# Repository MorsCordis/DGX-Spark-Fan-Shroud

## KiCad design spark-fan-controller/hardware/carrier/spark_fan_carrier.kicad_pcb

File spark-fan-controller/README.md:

# Spark fan controller

External 120 mm fan control for NVIDIA DGX Spark boxes in the
[DGX-Spark-Fan-Shroud](https://github.com/hyudryu/DGX-Spark-Fan-Shroud) (fork: MorsCordis).
The host service feeds the fan forward from GPU/CPU load with a temperature fallback.

## Layout

| Path | What |
|---|---|
| `host/spark_fan.py`, `host/spark-fan.service` | Host controller (runs on each Spark). Load-anticipating curve + thermal fallback, serial `DUTY 0..255` |
| `firmware/main_pwm_carrier.py` | MicroPython for the **Spark Fan Carrier** (GP28 PWM via open-drain FET, GP29 tach) |
| `firmware/main_x9c103.py` | Original repo firmware for the X9C103 + Owltree build (box #1) |
| `hardware/carrier/` | Spark Fan Carrier rev A: KiCad 10 schematic + PCB, generated from `design.py` |
| `hardware/carrier/fab/` | JLCPCB upload: `spark_fan_carrier_gerbers.zip`, `bom_jlc.csv`, `cpl_jlc.csv`, `bom_hand_solder.csv` |
| `hardware/enclosure/carrier_case.scad` | Parametric 3D-printed case for the carrier (+ `stl/`) |
| `hardware/enclosure/fan_guard.scad` | Bolt-on 120 mm intake guard + filter pocket + retainer (+ `stl/`, `stl/filter_template.svg`) |
| `hardware/enclosure/x9c103_box.scad` | Case for the original three-board build |
| `tests/` | `prefill_stress.py` (long-context prefill ramp via vLLM), `llm_stress.py`, `cooling_test.py` |
| `docs/` | Forum write-ups, stress logs, build guide for the X9C103 build |

## Spark Fan Carrier (rev A)

RP2040-Zero plugs into two 1x9 sockets. Its USB 5 V feeds an MT3608 boost to 12.36 V
(100k/5.1k feedback) for a 4-pin PWM fan header. GP28 drives fan pin 4 through a 2N7002
(open drain, inverted, gate pulled down, so a dead or unflashed RP2040 means full speed).
GP29 reads the tach through 1k with a 10k pull-up and 1 nF filter. 1.5 A PTC on the 5 V input,
green LED on 12 V. 24 x 50 mm, two layers, GND pour both sides, two M2.5 holes.

Rebuild everything (KiCad's bundled python):

```
cd hardware/carrier
"%LOCALAPPDATA%\Programs\KiCad\10.0\bin\python.exe" gen_sch.py
"%LOCALAPPDATA%\Programs\KiCad\10.0\bin\python.exe" gen_pcb.py
"%LOCALAPPDATA%\Programs\KiCad\10.0\bin\python.exe" fab.py
```

`design.py` is the single source for parts and nets; `gen_pcb.py` holds placement and routing.
Last check: ERC 0 violations, DRC 0 errors / 0 unconnected, schematic parity clean (remaining
warnings are silkscreen overlaps from the stock socket footprints).

Ordering at JLC (the board has SMD parts that are NOT practical to hand-solder, including the
MT3608, which DigiKey doesn't carry):
1. Upload `fab/spark_fan_carrier_gerbers.zip` (2 layers, 1.6 mm).
2. **Turn on "PCB Assembly"** below the board options. Without it JLC ships bare boards.
   Economic PCBA, top side, PCBA qty can be lower than the board qty.
3. Upload `fab/bom_jlc.csv` (BOM) and `fab/cpl_jlc.csv` (placement).
4. Check every part is matched, then check rotations in the placement preview (D1, D2, U1, Q1).

Before ordering:
- All 16 LCSC numbers in `fab/bom_jlc.csv` checked against JLC part pages on 2026-10-24
  (values, packages and ratings match). MT3608 and the LED are Extended parts.
- Check part rotations in JLC's placement preview (KiCad and JLC disagree on some footprints).
- J1/J2 (1x9 female, ~8.5 mm) and J3 (4-pin fan header) are hand-soldered.

Firmware: flash MicroPython, copy `firmware/main_pwm_carrier.py` to the board as `main.py`.
`host/spark_fan.py` works unchanged and now gets real `RPM` readings.

## Enclosure

`carrier_case.scad`: base + friction-fit lid, prints without supports (lid prints upside down).
USB-C opening, fan-cable slot, mounting ears, pinholes over BOOT/RESET. No screws: pegs on the
standoffs pass through H1/H2 and posts on the lid clamp the board (`fix = "screw"` restores
M2.5 self-tap pilots). Light pipes: Bivar PLPC2 press-fit from the top of the lid
(PLPC2-3MM over the Zero's RGB LED, PLPC2-500 over the 12 V LED, 2.0 mm hole with Bivar's
countersink); `pipes = "filament"` switches to clear 1.75 mm filament. Values marked `MEASURE`
(socket height, Zero LED/button positions) should be checked against real parts.
Outer size ~28.8 x 54.8 x 24.3 mm.

## Purchased parts

`hardware/bom_digikey_per_build.csv` is the DigiKey order for one build (carrier through-hole
parts, light pipes, fan guard magnets + filter, cable). Upload it in DigiKey's BOM Manager and
set the number of assemblies. The JLC-assembled SMD parts are in
`hardware/carrier/fab/bom_jlc.csv`; `hardware/carrier/fab/bom_digikey_smd.csv` is a DigiKey
fallback for hand assembly (no MT3608: DigiKey doesn't carry it; get it from LCSC C84817). RP2040-Zero boards come from Waveshare (not on DigiKey).

## Fan guard + filter

`fan_guard.scad`: hex grille plate that snaps onto the fan's intake side magnetically.
Default (`mount = "screw_head"`): drive the fan's bundled steel screws into the intake end of
the four holes; their heads sit in recesses on the guard's fan face (which also locate it) and
a 1/4" x 1/8" disc magnet (Radial Magnets 8193) sealed above each recess grabs them. Print fan-face down, pause at
z = 6.8 mm, drop the magnets in, resume. Measure the screw head (`head`, marked MEASURE) first.
`mount = "magnet"` glues 4 mm magnets into the holes instead (`stl/fan_guard_magnet.stl`, pause
at 4.0 mm; set polarity by sticking pairs together and marking the exposed face).
`mount = "screw"` is the bolt-on version (`stl/fan_guard_screw.stl`). An octagonal rim forms a pocket for a filter
up to `filter_max` (6.5 mm) thick; the retainer grid's skirt slides over the rim and stops on
the filter, so thin mesh and 1/4" foam both work. Adds 11.1 mm below the fan. Cut the
filter from `stl/filter_template.svg` (print at 100 %). Both parts print flat, no supports.

## To do

- [ ] Order carrier rev A, build, flash, bench test (12 V rail, PWM sweep, tach)
- [ ] Print + fit-check fan guard (fan hole diameter vs magnet, retainer `fit`)
- [ ] Multi-box dashboard (status endpoint in `spark_fan.py`)
- [ ] Filter-on vs filter-off prefill run at 2400 MHz
- [ ] Carrier, case, fan guard and carrier firmware stay private (possible product). Only the load-boost software is public (fork branch `feature/load-boost-controller`)

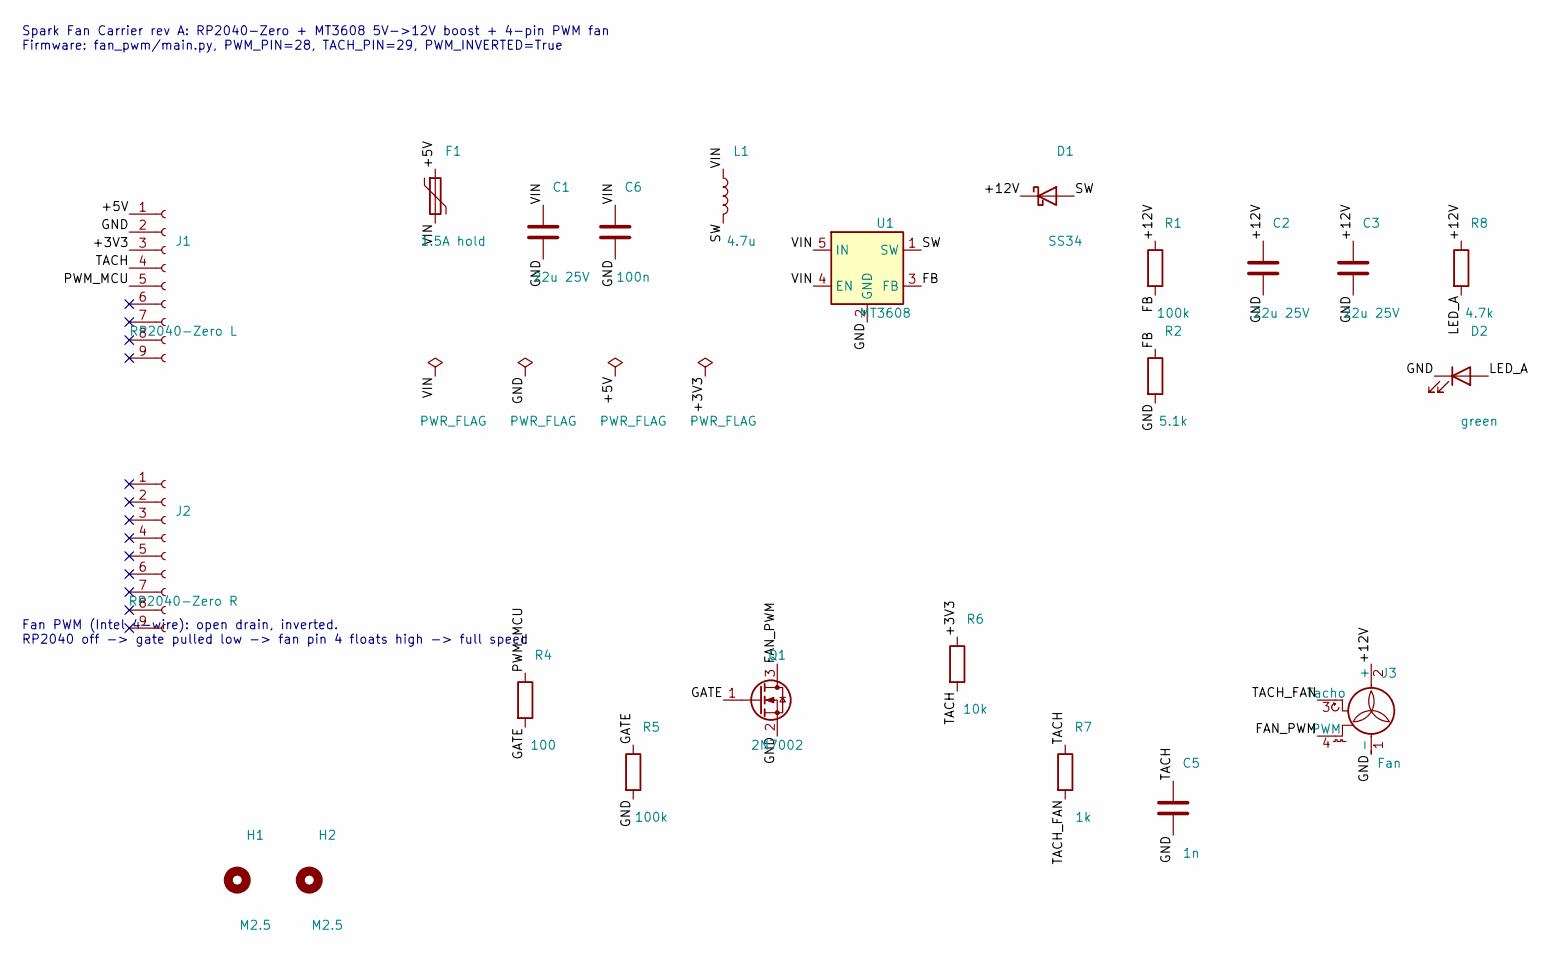
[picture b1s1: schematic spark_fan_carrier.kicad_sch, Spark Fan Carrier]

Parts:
C1: 22u 25V; C_0805_2012Metric; LCSC C45783
C2, C3: 22u 25V; C_1206_3216Metric; LCSC C12891
C5: 1n; C_0603_1608Metric; LCSC C1588
C6: 100n; C_0603_1608Metric; LCSC C14663
D1: SS34; D_SMA; LCSC C8678
D2: green; LED_0603_1608Metric; LCSC C72043
F1: 1.5A hold; Fuse_1206_3216Metric; MPN Eaton PTS12066V150; LCSC C2442501
H1, H2: M2.5; MountingHole_2.7mm_M2.5
J1: RP2040-Zero L; PinSocket_1x09_P2.54mm_Vertical
J2: RP2040-Zero R; PinSocket_1x09_P2.54mm_Vertical
J3: Fan; FanPinHeader_1x04_P2.54mm_Vertical
L1: 4.7u; L_Sunlord_SWPA5040S; MPN Sunlord SWPA5040S4R7MT; LCSC C48496
Q1: 2N7002; SOT-23; LCSC C8545
R1, R5: 100k; R_0603_1608Metric; LCSC C25803
R2: 5.1k; R_0603_1608Metric; LCSC C23186
R4: 100; R_0603_1608Metric; LCSC C22775
R6: 10k; R_0603_1608Metric; LCSC C25804
R7: 1k; R_0603_1608Metric; LCSC C21190
R8: 4.7k; R_0603_1608Metric; LCSC C23162
U1: MT3608; SOT-23-6; LCSC C84817

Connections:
/+3V3: J1.3, R6.1
/+5V: F1.1, J1.1
/+12V: C2.1, C3.1, D1.1 (K), J3.2 (+), R1.1, R8.1
/FAN_PWM: J3.4 (PWM), Q1.3 (D)
/FB: R1.2, R2.1, U1.3 (FB)
/GATE: Q1.1 (G), R4.2, R5.1
/GND: C1.2, C2.2, C3.2, C5.2, C6.2, D2.1 (K), J1.2, J3.1 (-), Q1.2 (S), R2.2, R5.2, U1.2 (GND)
/LED_A: D2.2 (A), R8.2
/PWM_MCU: J1.5, R4.1
/SW: D1.2 (A), L1.2, U1.1 (SW)
/TACH: C5.1, J1.4, R6.2, R7.1
/TACH_FAN: J3.3 (Tacho), R7.2
/VIN: C1.1, C6.1, F1.2, L1.1, U1.4 (EN), U1.5 (IN)

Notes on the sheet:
Spark Fan Carrier rev A: RP2040-Zero + MT3608 5V->12V boost + 4-pin PWM fan Firmware: fan_pwm/main.py, PWM_PIN=28, TACH_PIN=29, PWM_INVERTED=True
Fan PWM (Intel 4-wire): open drain, inverted. RP2040 off -> gate pulled low -> fan pin 4 floats high -> full speed

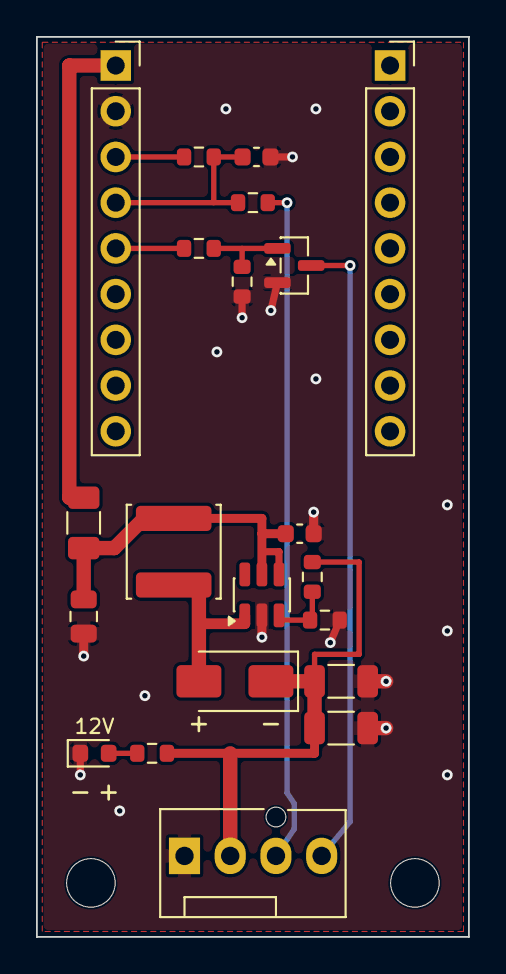
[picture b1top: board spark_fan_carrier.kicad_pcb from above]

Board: 2 copper layers, 24.0 x 50.0 mm, 23 parts (0 on the bottom side), 13 nets.

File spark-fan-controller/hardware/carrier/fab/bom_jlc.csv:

Comment,Designator,Footprint,LCSC Part #,MPN / note
22u 25V,C1,C_0805_2012Metric,C45783,
22u 25V,"C2,C3",C_1206_3216Metric,C12891,
1n,C5,C_0603_1608Metric,C1588,
100n,C6,C_0603_1608Metric,C14663,
SS34,D1,D_SMA,C8678,
red,D2,LED_0603_1608Metric,C2286,
1.5A hold,F1,Fuse_1206_3216Metric,C20802,Ruilon SMD1206P150TF
4.7u,L1,L_Sunlord_SWPA5040S,C48496,Sunlord SWPA5040S4R7MT
2N7002,Q1,SOT-23,C8545,
100k,"R1,R5",R_0603_1608Metric,C25803,
5.1k,R2,R_0603_1608Metric,C23186,
100,R4,R_0603_1608Metric,C22775,
10k,R6,R_0603_1608Metric,C25804,
1k,R7,R_0603_1608Metric,C21190,
4.7k,R8,R_0603_1608Metric,C23162,
MT3608,U1,SOT-23-6,C84817,

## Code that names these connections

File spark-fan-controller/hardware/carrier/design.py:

"""Spark Fan Carrier: single source of truth for parts and nets.

RP2040-Zero plugs into J1/J2. Its USB 5 V feeds an MT3608 boost to 12 V for a
4-pin PWM fan. GP28 drives the fan PWM line through an open-drain 2N7002
(inverted, fails to full speed), GP29 reads the tach.

Each part: ref -> (lib_id, value, footprint, sch_xy, {pin: net or None}, fields)
None marks an intentionally unconnected pin.
"""

PROJECT = "spark_fan_carrier"
TITLE = "Spark Fan Carrier"
REV = "A"

FP_R = "Resistor_SMD:R_0603_1608Metric"
FP_C0603 = "Capacitor_SMD:C_0603_1608Metric"

# Verify every LCSC number on lcsc.com before ordering.
PARTS = {
    # RP2040-Zero sockets. J1 is the 5V/GND/3V3/GP29/GP28.. row, J2 (GP0..GP8) is mechanical only.
    "J1": ("Connector:Conn_01x09_Socket", "RP2040-Zero L", "Connector_PinSocket_2.54mm:PinSocket_1x09_P2.54mm_Vertical",
           (50.8, 63.5), {"1": "+5V", "2": "GND", "3": "+3V3", "4": "TACH", "5": "PWM_MCU",
                          "6": None, "7": None, "8": None, "9": None}, {}),
    "J2": ("Connector:Conn_01x09_Socket", "RP2040-Zero R", "Connector_PinSocket_2.54mm:PinSocket_1x09_P2.54mm_Vertical",
           (50.8, 101.6), {str(i): None for i in range(1, 10)}, {}),
    # 5 V input
    "F1": ("Device:Polyfuse", "1.5A hold", "Fuse:Fuse_1206_3216Metric",
           (88.9, 50.8), {"1": "+5V", "2": "VIN"}, {"LCSC": "C20802", "MPN": "Ruilon SMD1206P150TF"}),
    "C1": ("Device:C", "22u 25V", "Capacitor_SMD:C_0805_2012Metric",
           (104.14, 55.88), {"1": "VIN", "2": "GND"}, {"LCSC": "C45783"}),
    "C6": ("Device:C", "100n", FP_C0603,
           (114.3, 55.88), {"1": "VIN", "2": "GND"}, {"LCSC": "C14663"}),
    # Boost 5 V -> 12.36 V (Vfb 0.6 V: 0.6 * (1 + 100k/5.1k))
    "L1": ("Device:L", "4.7u", "Inductor_SMD:L_Sunlord_SWPA5040S",
           (129.54, 50.8), {"1": "VIN", "2": "SW"}, {"LCSC": "C48496", "MPN": "Sunlord SWPA5040S4R7MT"}),
    "U1": ("Regulator_Switching:MT3608", "MT3608", "Package_TO_SOT_SMD:SOT-23-6",
           (149.86, 60.96), {"1": "SW", "2": "GND", "3": "FB", "4": "VIN", "5": "VIN", "6": None},
           {"LCSC": "C84817"}),
    "D1": ("Device:D_Schottky", "SS34", "Diode_SMD:D_SMA",
           (175.26, 50.8), {"1": "+12V", "2": "SW"}, {"LCSC": "C8678"}),
    "R1": ("Device:R", "100k", FP_R, (190.5, 60.96), {"1": "+12V", "2": "FB"}, {"LCSC": "C25803"}),
    "R2": ("Device:R", "5.1k", FP_R, (190.5, 76.2), {"1": "FB", "2": "GND"}, {"LCSC": "C23186"}),
    "C2": ("Device:C", "22u 25V", "Capacitor_SMD:C_1206_3216Metric",
           (205.74, 60.96), {"1": "+12V", "2": "GND"}, {"LCSC": "C12891"}),
    "C3": ("Device:C", "22u 25V", "Capacitor_SMD:C_1206_3216Metric",
           (218.44, 60.96), {"1": "+12V", "2": "GND"}, {"LCSC": "C12891"}),
    # 12 V indicator
    "R8": ("Device:R", "4.7k", FP_R, (233.68, 60.96), {"1": "+12V", "2": "LED_A"}, {"LCSC": "C23162"}),
    "D2": ("Device:LED", "red", "LED_SMD:LED_0603_1608Metric",
           (233.68, 76.2), {"1": "GND", "2": "LED_A"}, {"LCSC": "C2286"}),
    # Fan PWM: open drain, inverted. Gate pulldown keeps the FET off (fan at
    # full speed via its internal pull-up) whenever the RP2040 isn't driving.
    "R4": ("Device:R", "100", FP_R, (101.6, 121.92), {"1": "PWM_MCU", "2": "GATE"}, {"LCSC": "C22775"}),
    "R5": ("Device:R", "100k", FP_R, (116.84, 132.08), {"1": "GATE", "2": "GND"}, {"LCSC": "C25803"}),
    "Q1": ("Transistor_FET:2N7002", "2N7002", "Package_TO_SOT_SMD:SOT-23",
           (134.62, 121.92), {"1": "GATE", "2": "GND", "3": "FAN_PWM"}, {"LCSC": "C8545"}),
    # Tach: open collector from the fan through 1k, pulled up to 3V3 at the RP2040, 1n filter.
    "R6": ("Device:R", "10k", FP_R, (162.56, 116.84), {"1": "+3V3", "2": "TACH"}, {"LCSC": "C25804"}),
    "R7": ("Device:R", "1k", FP_R, (177.8, 132.08), {"1": "TACH", "2": "TACH_FAN"}, {"LCSC": "C21190"}),
    "C5": ("Device:C", "1n", FP_C0603, (193.04, 137.16), {"1": "TACH", "2": "GND"}, {"LCSC": "C1588"}),
    "J3": ("Motor:Fan_4pin", "Fan", "Connector:FanPinHeader_1x04_P2.54mm_Vertical",
           (220.98, 124.46), {"1": "GND", "2": "+12V", "3": "TACH_FAN", "4": "FAN_PWM"}, {}),
    # Power flags for ERC
    "#FLG01": ("power:PWR_FLAG", "PWR_FLAG", "", (88.9, 76.2), {"1": "VIN"}, {}),
    "#FLG02": ("power:PWR_FLAG", "PWR_FLAG", "", (101.6, 76.2), {"1": "GND"}, {}),
    "#FLG03": ("power:PWR_FLAG", "PWR_FLAG", "", (114.3, 76.2), {"1": "+5V"}, {}),
    "#FLG04": ("power:PWR_FLAG", "PWR_FLAG", "", (127.0, 76.2), {"1": "+3V3"}, {}),
    "H1": ("Mechanical:MountingHole", "M2.5", "MountingHole:MountingHole_2.7mm_M2.5",
           (60.96, 147.32), {}, {}),
    "H2": ("Mechanical:MountingHole", "M2.5", "MountingHole:MountingHole_2.7mm_M2.5",
           (71.12, 147.32), {}, {}),
}

NOTES = [
    ((30.48, 30.48), "Spark Fan Carrier rev A: RP2040-Zero + MT3608 5V->12V boost + 4-pin PWM fan\n"
                     "Firmware: fan_pwm/main.py, PWM_PIN=28, TACH_PIN=29, PWM_INVERTED=True"),
    ((30.48, 114.3), "Fan PWM (Intel 4-wire): open drain, inverted.\n"
                     "RP2040 off -> gate pulled low -> fan pin 4 floats high -> full speed"),
]


def nets():
    out = {}
    for ref, (_, _, _, _, pinmap, _) in PARTS.items():
        for pin, net in pinmap.items():
            if net:
                out.setdefault(net, set()).add((ref, pin))
    return out
